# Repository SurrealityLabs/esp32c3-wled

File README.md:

# esp32c3-wled
PCB for mounting an ESP32-C3 board and attaching Neopixels

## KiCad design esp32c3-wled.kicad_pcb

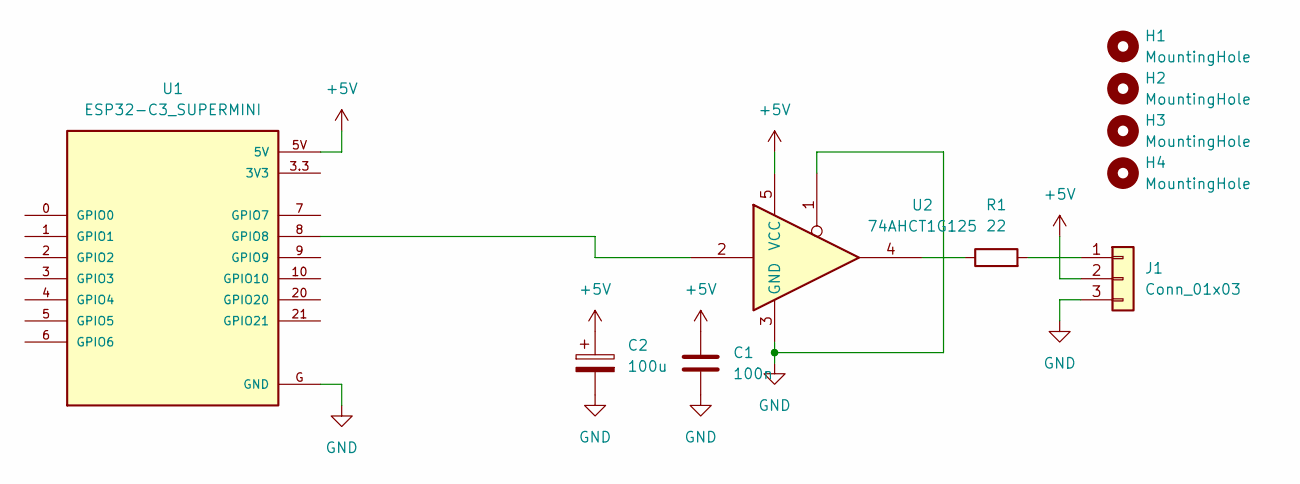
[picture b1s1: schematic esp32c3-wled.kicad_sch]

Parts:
C1: 100n; C_0603_1608Metric; LCSC C14663
C2: 100u; CP_Elec_8x10.5; LCSC C401846
H1, H2, H3, H4: MountingHole; MountingHole_3.2mm_M3_ISO7380
J1: Conn_01x03; JST_PH_S3B-PH-SM4-TB_1x03-1MP_P2.00mm_Horizontal; LCSC C707033
R1: 22; R_0603_1608Metric; LCSC C23345
U1: ESP32-C3_SUPERMINI; MODULE_ESP32-C3_SUPERMINI
U2: 74AHCT1G125; SOT-353_SC-70-5; LCSC C151417

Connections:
+5V: C1.1, C2.1, J1.2, U1.5V, U2.5 (VCC)
GND: C1.2, C2.2, J1.3, U1.G (GND), U2.1, U2.3 (GND)
unnamed: J1.1, R1.2
unnamed: R1.1, U2.4
unnamed: U1.8 (GPIO8), U2.2

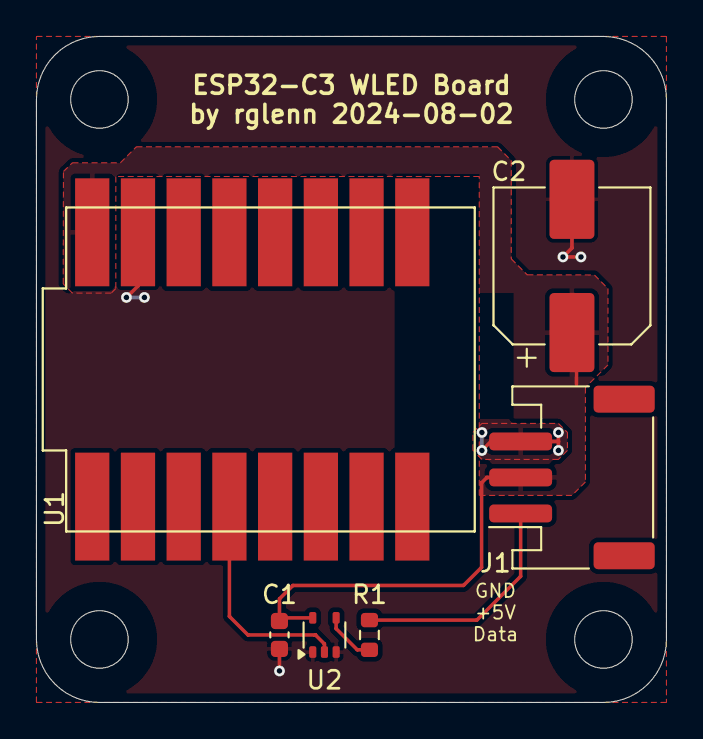
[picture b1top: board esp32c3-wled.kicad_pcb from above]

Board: 2 copper layers, 35.0 x 37.0 mm, 10 parts (0 on the bottom side), 5 nets.

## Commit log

2024-09-09 Adding updated board with cutout in planes for antenna
